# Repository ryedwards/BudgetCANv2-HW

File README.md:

# BudgetCANv2-HW
BudgetCANv2 hardware in Eagle format

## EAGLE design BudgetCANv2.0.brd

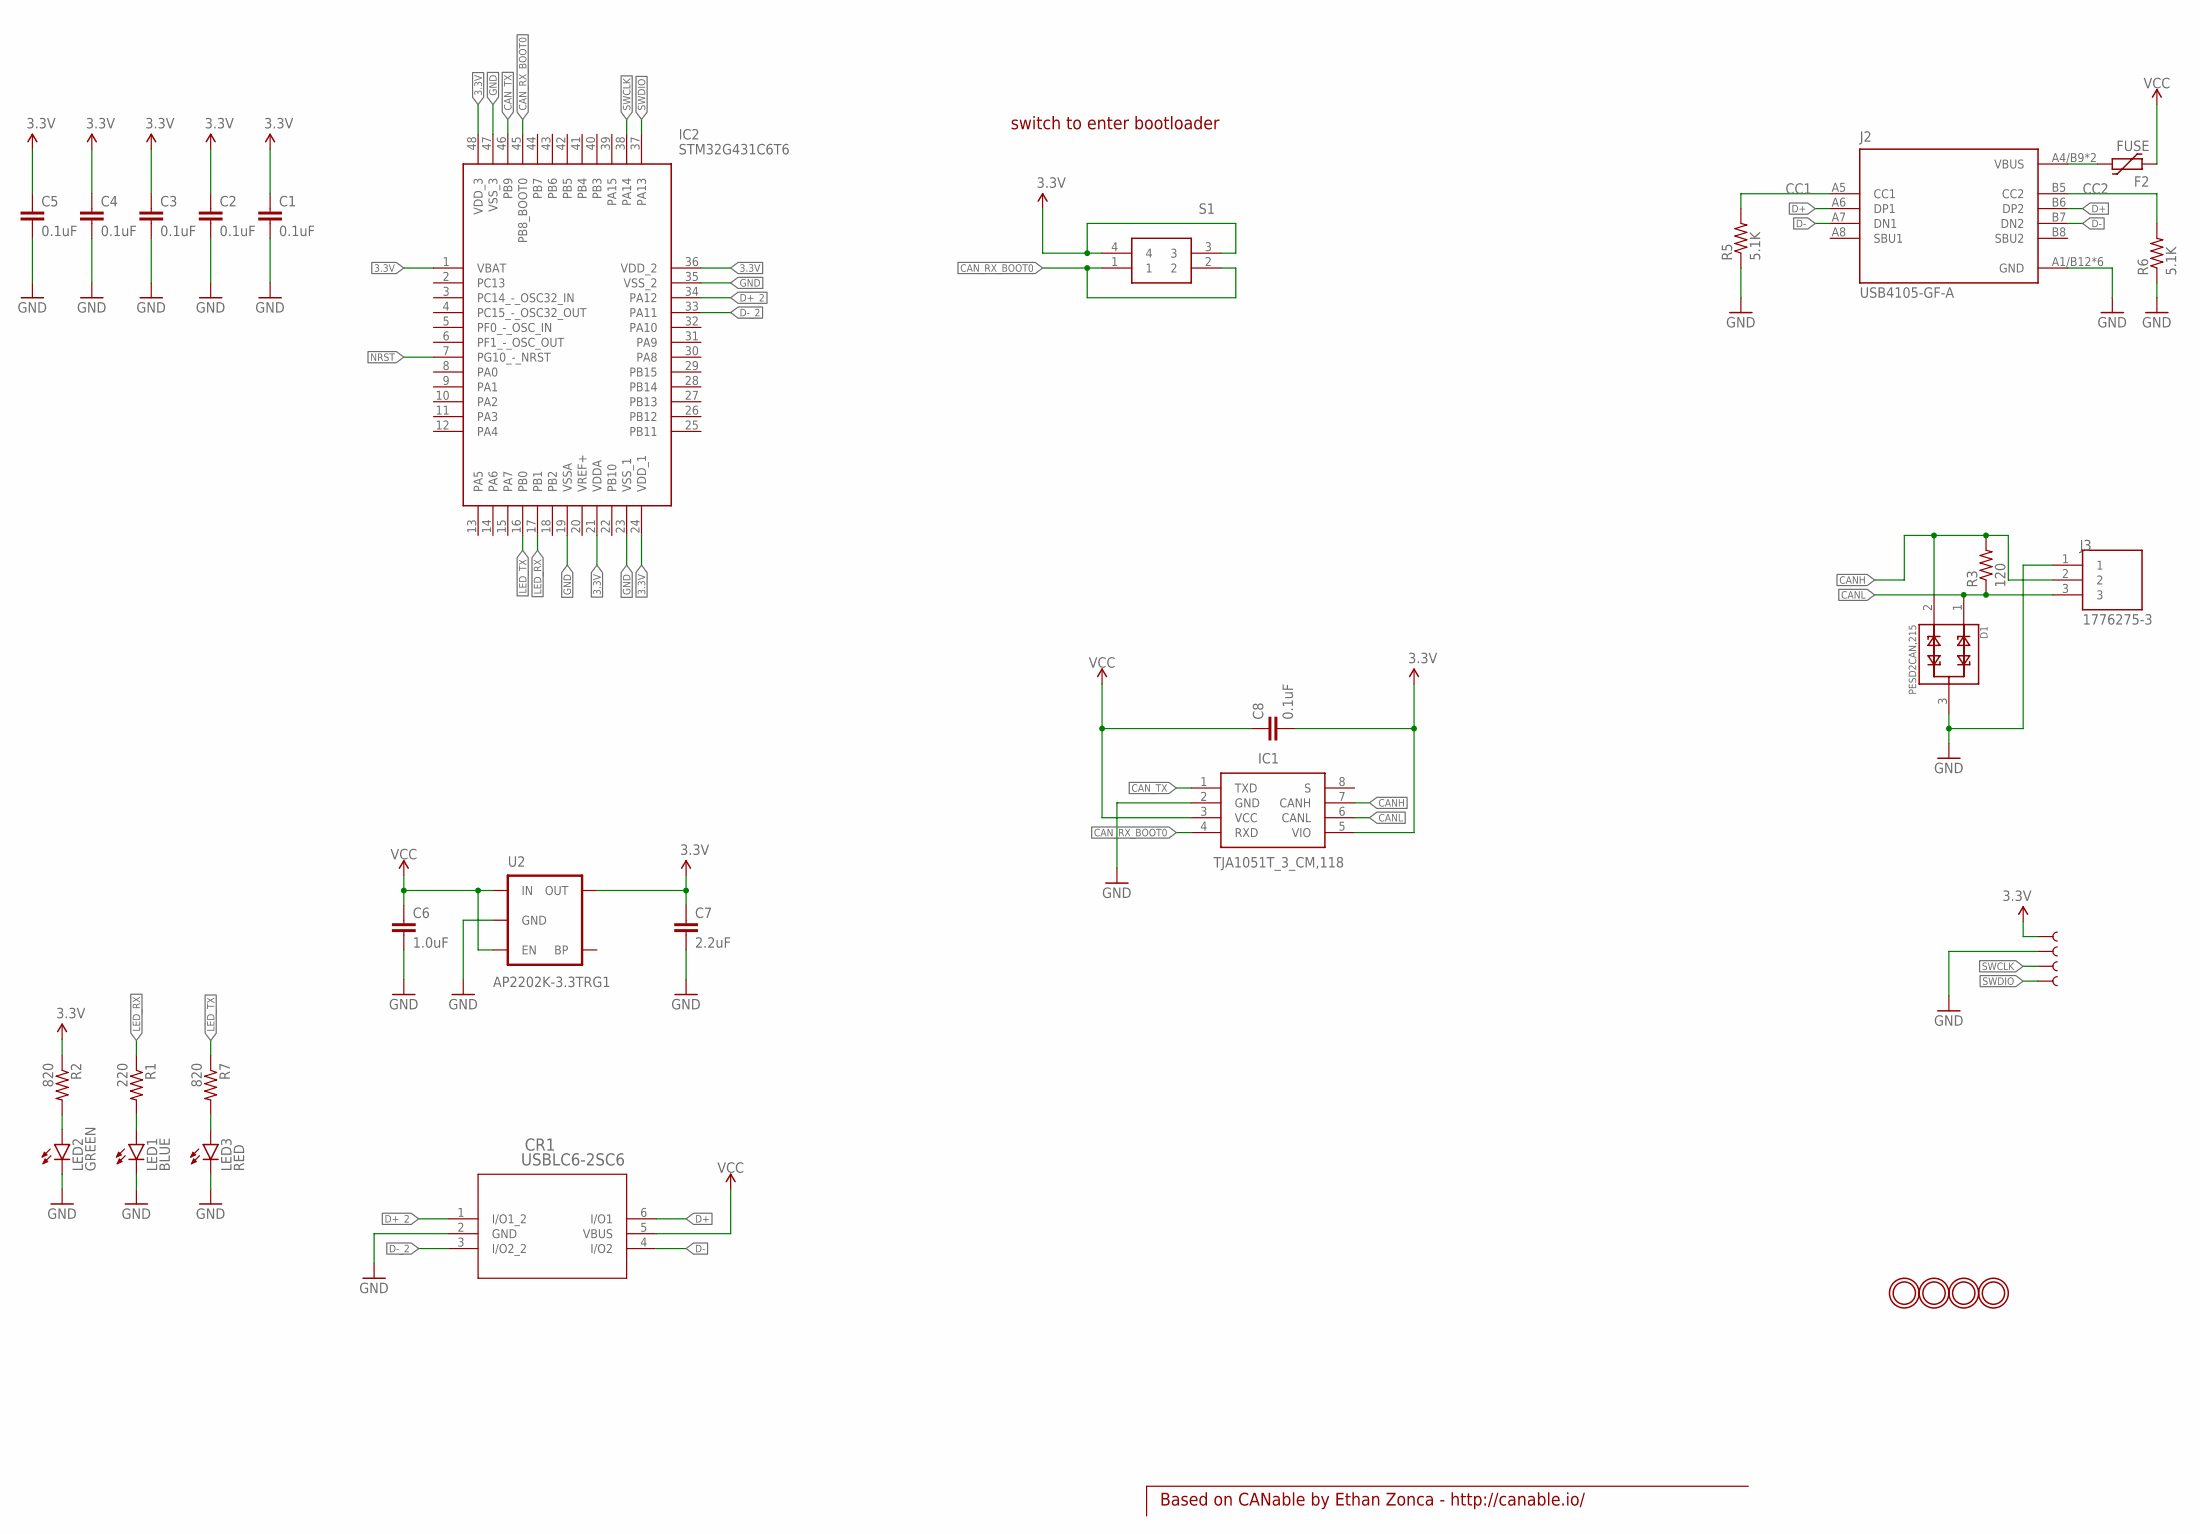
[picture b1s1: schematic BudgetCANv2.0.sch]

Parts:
C1, C2, C3, C4, C5, C8: 0.1uF; 0603-CAP
C6: 1.0uF; 0603-CAP
C7: 2.2uF; 0603-CAP
CR1: USBLC6-2SC6; SOT23-6L
D1: PESD2CAN,215; SOT95P230X110-3N
F2: FUSE; PTC0805
IC1: TJA1051T_3_CM,118; SOIC127P600X175-8N
IC2: STM32G431C6T6; QFP50P900X900X160-48N
J2: USB4105-GF-A; GCT_USB4105-GF-A
J3: 1776275-3; TE_1776275-3
LED1: BLUE; LED-0603
LED2: GREEN; LED-0603
LED3: RED; LED-0603
R1: 220; 0603-RES
R2, R7: 820; 0603-RES
R3: 120; 0603-RES
R5, R6: 5.1K; 0603-RES
S1: KMR631NGULCLFS; KMR621NG
TP1, TP2, TP3, TP4: TEST-POINT3X5; PAD.03X.05
U2: AP2202K-3.3TRG1; SOT23-5
U$2, U$3, U$4, U$5: MOUNTINGHOLE3.0THIN; MOUNTINGHOLE_3.0_PLATEDTHIN

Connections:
3.3V: C1.1, C2.1, C3.1, C4.1, C5.1, C7.1, C8.2, IC1.5 (VIO), IC2.1 (VBAT), IC2.21 (VDDA), IC2.24 (VDD_1), IC2.36 (VDD_2), IC2.48 (VDD_3), R2.1, S1.3, S1.4, TP1.P$1, U2.5 (OUT)
CANH: D1.2, IC1.7 (CANH), J3.2, R3.2
CANL: D1.1, IC1.6 (CANL), J3.3, R3.1
CAN_RX_BOOT0: IC1.4 (RXD), IC2.45 (PB8_BOOT0), S1.1, S1.2
CAN_TX: IC1.1 (TXD), IC2.46 (PB9)
CC1: J2.A5 (CC1), R5.2
CC2: J2.B5 (CC2), R6.2
D+: CR1.6 (I/O1), J2.A6 (DP1), J2.B6 (DP2)
D+_2: CR1.1 (I/O1_2), IC2.34 (PA12)
D-: CR1.4 (I/O2), J2.A7 (DN1), J2.B7 (DN2)
D-_2: CR1.3 (I/O2_2), IC2.33 (PA11)
GND: C1.2, C2.2, C3.2, C4.2, C5.2, C6.2, C7.2, CR1.2 (GND), D1.3, IC1.2 (GND), IC2.19 (VSSA), IC2.23 (VSS_1), IC2.35 (VSS_2), IC2.47 (VSS_3), J2.A1/B12 (GND), J2.B1/A12 (GND), J2.G1 (GND), J2.G2 (GND), J2.G3 (GND), J2.G4 (GND), J3.1, LED1.C, LED2.C, LED3.C, R5.1, R6.1, TP2.P$1, U2.2 (GND)
LED_BLUE: LED1.A, R1.2
LED_GREEN: LED2.A, R2.2
LED_RED: LED3.A, R7.2
LED_RX: IC2.17 (PB1), R1.1
LED_TX: IC2.16 (PB0), R7.1
NRST: IC2.7 (PG10_-_NRST)
SWCLK: IC2.38 (PA14), TP3.P$1
SWDIO: IC2.37 (PA13), TP4.P$1
VBUS: F2.2, J2.A4/B9 (VBUS), J2.B4/A9 (VBUS)
VCC: C6.1, C8.1, CR1.5 (VBUS), F2.1, IC1.3 (VCC), U2.1 (IN), U2.3 (EN)

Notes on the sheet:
Based on CANable by Ethan Zonca - http://canable.io/
switch to enter bootloader

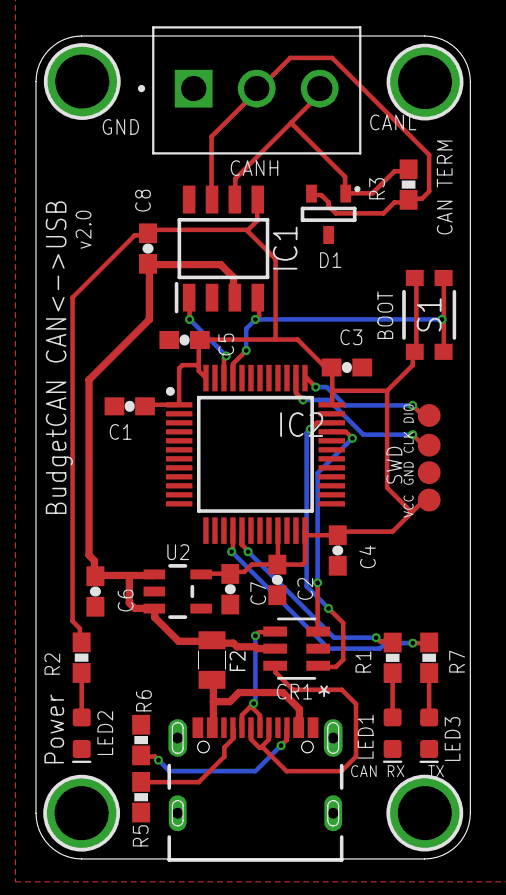
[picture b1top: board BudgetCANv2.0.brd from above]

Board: 2 copper layers, 24.1 x 45.7 mm, 34 parts (0 on the bottom side), 21 nets.

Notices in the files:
parts and their libraries:
SparkFun-Passives: Licensing: Creative Commons ShareAlike 4.0 International - https://creativecommons.org/licenses/by-sa/4.0
